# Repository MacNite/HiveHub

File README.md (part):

# HiveHub

> **Project renamed: HiveScale → HiveHub.** The project outgrew its original
> "dual scale" scope and now acts as a **data collector / hub for many different
> types of beehive sensors and scales** (up to 18 hives per ESP32), so the name
> was changed to match. A few internal identifiers — the database measurement
> columns, the OTA `target` value, the Docker image name (`…/hivescale-api`), the
> device's stored-config (NVS) namespace and MQTT topics — still use the old
> `hivescale` name on purpose: changing them would need data/firmware migrations
> and could strand existing measurements or deployed-device config. The
> third-party **beehivemonitoring.com "HiveScale"** wireless weight scale is an
> unrelated product and keeps its own name.

**Hardware status: all published PCBs are tested and working.** The recommended build is the **XIAO ESP32-C6 on the Scale Module V0.4** with **NAU7802**, **MAX17048**, **TPS63020**, **TP4056**, RTC, SD card and SHT40 — optionally expanded to **16 scales** with the NAU7802 breakout PCB (TCA9548A mux + up to 8× NAU7802). See [pcb-design/README.md](pcb-design/README.md). The old ESP32 30-pin board is obsolete and no longer recommended.

**HiveHub is an ESP32-based data collector for beehive sensors and scales.** It
gathers weight, temperature, humidity, sound, vibration, power state, and network
state from one or more hives (up to 18 per ESP32) and sends the readings to a
self-hosted FastAPI backend backed by PostgreSQL, where they can be displayed in
[HivePal](https://github.com/martinhrvn/hive-pal).

### Natively supported sensors

Every sensor is optional and compiled in per device — HiveHub reads the
following directly on the ESP32:

- **Ambient sensor (SHT4x / SHT3x / BME280)** — one device-level outside-hive
  sensor on the shared I2C bus, selectable at build time: SHT4x/SHT40 (default)
  or SHT3x for temperature + humidity, or a BME280 which additionally reports
  barometric pressure (`ambient_pressure_hpa`).
- **DS18B20** — per-hive in-hive temperature probes (1-Wire).
- **INMP441** — in-hive sound via I2S MEMS microphones with per-band FFT.
- **MAX17048** — LiPo battery voltage, state-of-charge, and low-battery alerts (I2C).
- **Wired load cells via HX711 or NAU7802** — the hive scales themselves; NAU7802
  over I2C (optionally behind a TCA9548A mux) scales to many channels for
  multi-hive setups.

On top of these wired sensors, HiveHub also bridges a range of wireless BLE/GATT
sensors and scales (HolyIot, RuuviTag, HiveInside, and beehivemonitoring.com
HiveHeart / HiveScale devices) — see [Features](#features) below.

> 🌐 **Website & setup guide:** a small static site lives in [`website/`](website/) — a
> feature overview, a step-by-step setup guide, a complete
> ["Build your own" guide](website/build.html) (BOM with price estimates, wiring,
> firmware, backend — downloadable as PDF), and an in-browser
> [`secrets.h` configurator](website/configurator.html) that builds your firmware
> config (sensors, BLE/GATT options, power modules) without hand-editing macros.
> It deploys to GitHub Pages via `.github/workflows/pages.yml`
> (enable **Settings → Pages → Source: GitHub Actions**), e.g.
> `https://macnite.github.io/HiveHub/`.

---

## Features

Every sensor is optional and compiled in per device — start with weight and add the rest.

- **Dual load cells** — two HX711 amplifiers drive two independent hive scales (the one always-on measurement).
- **Backend load-cell temperature compensation** — corrects HX711 thermal drift on read from the stored raw values; see [docs/temperature-compensation.md](docs/temperature-compensation.md).
- **Per-hive temperature** — optional DS18B20 probes on a shared 1-Wire bus (off by default), or an in-hive BLE sensor as the source.
- **Per-hive in-hive sound** — optional INMP441 stereo I2S microphones with per-band FFT (off by default).
- **Per-hive vibration** — from a paired in-hive BLE sensor (a HiveInside nRF54LM20A gives full FFT bands; a HolyIot/RuuviTag beacon gives a low-rate magnitude), capturing the ~20 Hz pre-swarm signal microphones miss. (The old wired LIS3DH/LIS2DH12 driver has been removed — in-hive vibration is BLE-only.)
- **In-hive BLE sensors** — pair up to two battery beacons (HolyIot 25015, RuuviTag, HiveInside nRF54LM20A, or beehivemonitoring.com HiveHeart) for temperature/humidity/pressure/vibration with no wiring. Note that a HiveHeart is read over GATT and accepts only **one** connection at a time, so HiveHub, the beehivemonitoring Hub and the beehivemonitoring app cannot share one — see [beehivemonitoring-gatt.md](docs/beehivemonitoring-gatt.md#one-reader-at-a-time).
- **Ambient temperature & humidity** — one selectable device-level I2C sensor: SHT4x/SHT40 (default), SHT3x, or a BME280 that also reports barometric pressure (`ambient_pressure_hpa`). Picked at build time (`ENABLE_SHT4X_AMBIENT` / `ENABLE_SHT3X_AMBIENT` / `ENABLE_BME280_AMBIENT`).
- **RTC timekeeping** — a DS3231 timestamps measurements without depending on NTP.
- **SD card cache & backup** — local buffering when uploads fail, plus an append-only persistent backup that can be downloaded in AP mode and re-imported via HivePal.
- **Claim-code pairing** — claim devices from HivePal without manual database setup.
- **Remote configuration & commands** — sampling interval, scale offsets/factors, calibration, OTA checks, provisioning, reboot, Wi-Fi reset, and factory reset.
- **OTA firmware updates** — owner-scoped releases with an accept-to-apply gate; the device also relays firmware over BLE GATT to a HiveInside sensor or a HiveTraffic counter. Both relays are version-gated and explicit: publishing a release never pushes it to a sub-device on its own.
- **Wi-Fi provisioning portal** — opened by the setup button (or remotely with a `start_provisioning` command) for field configuration, including pairing wireless sensors.
- **[Inspection mode](docs/inspection-mode.md)** — one press of the external button, a dashboard switch or a HivePal API call marks the window while a hive is open, so the 40 kg step from lifting two supers stays out of the charts, insights and alert rules. Nothing is deleted: the readings remain in the database and in every export.
- **Multi-network Wi-Fi** — up to three saved networks.
- **Hive audio (optional)** — ask a paired HiveInside node (firmware 0.6.2+) to record 10–60 seconds from inside the hive, then play it back in the dashboard. The hub collects the request on its next wake, so a recording arrives within one reporting interval rather than instantly. Authenticated with a shared key and stored as WAV on your own server. Useful for checking what an insight flagged — or just for listening to the bees. See [Listening to a hive](docs/audio-recording.md).
- **Insights** — backend auto-evaluation of weight, temperature, sound, vibration, and entrance traffic per hive, based on [these publications](docs/insights-sources-tldr.md).
- **Insight alert notifications (optional)** — get swarm / robbing / winter-risk alerts by **e-mail (SMTP)** and/or **Web Push** to your phone or an installable dashboard PWA (Android, iOS 16.4+, desktop) when an insight first fires or escalates. Off by default; see [Insight alert notifications](docs/notifications.md).
- **Optional off-grid mode** — solar/LiPo charging (CN3791 MPPT + TPS63020) with MAX17048 LiPo telemetry.
- **Optional entrance bee counters** — wireless [HiveTraffic](docs/hivetraffic-bee-counter.md) counters over **BLE/GATT only** (wired I2C BeeCounters are no longer supported).
- **Built-in web dashboard (optional)** — a dependency-free dashboard served from the backend at `/dashboard` for single-owner self-hosts, protected by **username + password login** (first visit runs a setup wizard; admin/viewer roles): cross-device hive comparison, charts for every data group, plus device-config editing, hive renaming, firmware/OTA and calibration controls, SD-backup import, and user management. Off by default (`ENABLE_LOCAL_DASHBOARD`); see [server/dashboard/README.md](server/dashboard/README.md) and the [live demo](https://macnite.github.io/HiveHub/dashboard-demo/).
- **Publish data for your website** — from **Device & admin → Publish data**, publish one chart (a metric, the hives you pick, a rolling period) and embed it in a club page, blog or shop with a one-line `<iframe>` — or fetch the same slice as JSON/CSV and draw it yourself. Everything else stays behind the login: a published link exposes only the labels you typed, no device IDs or other readings, and can be revoked at any time. See [Publish data](docs/publish-embed.md).
- **[HivePal](https://github.com/martinhrvn/hive-pal) integration** — dedicated `/api/v1/app/...` endpoints using a HivePal service key, per-user JWTs, and per-user access roles.
- **Optional MQTT bridge** — mirror every reading to an MQTT broker (Home Assistant, Node-RED, openHAB…) with Home Assistant auto-discovery, alongside the built-in PostgreSQL store. Off by default; see [MQTT / Home Assistant integration](#mqtt--home-assistant-integration).
- **PCB designs (tested and working)** — KiCad ESP32-C6 Scale Module (recommended) and NAU7802 breakout board with fabrication outputs, plus the Power Module and legacy 30-pin Scale Module.
- **Docker Compose deployment** — the API and PostgreSQL database.

---

## Repository structure

```text
HiveHub/
├── firmware/                   # ESP32 PlatformIO project (src/, include/)
├── server/                     # Python FastAPI backend, insights, migrations
│   ├── dashboard/              # Built-in login-protected web dashboard (served at /dashboard)
│   └── embed/                  # Public "Publish data" chart pages (served at /embed/chart/<token>)
├── docker/                     # Docker Compose deployment
├── website/                    # Static site + secrets.h configurator (GitHub Pages)
│   └── dashboard-demo/         # Backend-free dashboard demo (sample data)
├── docs/                       # Hardware, API, deployment, and feature docs
├── pcb-design/                 # KiCad breakout PCB design and fabrication files
├── test-data/                  # Mock server and decoder/insight unit tests
└── .github/workflows/          # CI: backend image build + website Pages deploy
```

---

## Hardware

### Core components

All links are affiliate links and support this project directly.

The recommended build is the **XIAO ESP32-C6 on the Scale Module V0.4** — the complete
bill of materials with price estimates and shop links lives on the
[**Build your own** page](website/build.html) (also downloadable as
[CSV](website/assets/hivehub-bom.csv)).

| Component | Role |
|---|---|
| Seeed Studio XIAO ESP32-C6 | Main controller (**recommended** — plugs into the Scale Module V0.4 PCB) |
| NAU7802 (I2C, on the Scale Module / breakout PCB) + [load cells](https://s.click.aliexpress.com/e/_c33VsCl7) | Weight measurement (**recommended** — 2 scales on the Scale Module, up to 16 via the NAU7802 breakout PCB with its TCA9548A mux + up to 8× NAU7802) |
| [SHT4x / SHT40](https://s.click.aliexpress.com/e/_c3CvaIKz) (or SHT3x / BME280) | Ambient temperature and humidity (BME280 also adds barometric pressure) |
| [DS3231 RTC](https://s.click.aliexpress.com/e/_c4mfPBtR) | Offline timekeeping (remove its 4.7 kΩ I2C pull-ups — see the I2C pull-up note in [docs/wiring.md](docs/wiring.md)) |
| [MicroSD card module](https://s.click.aliexpress.com/e/_c3oDcFM9) + card | Local cache and backup storage |
| [MAX17048](https://s.click.aliexpress.com/e/_c3JKEzrL) | LiPo battery gauge (on the Scale Module) |
| [TPS63020 buck-boost](https://s.click.aliexpress.com/e/_c2uscIy1) | Battery/5 V input to the regulated 3.3 V rail |
| [TP4056 USB-C charger](https://s.click.aliexpress.com/e/_c4beU1nL) | LiPo charging |
| [Momentary pushbutton](https://s.click.aliexpress.com/e/_c4sqg7Lx) | Provisioning and factory reset |
| [IP-rated enclosure](https://s.click.aliexpress.com/e/_c30msn9R), [glands](https://de.aliexpress.com/item/1005007921366362.html), frame hardware | Outdoor installation |
| [ESP32 Dev Board](https://s.click.aliexpress.com/e/_c3LV3nfF) + 2x [HX711](https://s.click.aliexpress.com/e/_c3DkGsAN) | Legacy 30-pin build (obsolete — no longer recommended) |

### Optional sensors (enable per device in `secrets.h`)

| Component | Firmware flag | Role |
|---|---|---|
| 2x [DS18B20 waterproof probes](https://s.click.aliexpress.com/e/_c4X4ktmv) | `ENABLE_DS18B20_HIVE_TEMP` | Internal hive temperature (or use an in-hive BLE sensor) |
| 2x [INMP441 sound sensors](https://s.click.aliexpress.com/e/_c313NoAd) | `ENABLE_INMP441_MICS` | Internal hive sound with per-band FFT |
| [MAX17048](https://s.click.aliexpress.com/e/_c3JKEzrL) | `ENABLE_MAX17048_BATTERY` | LiPo voltage, state-of-charge, and low-battery alert |
| In-hive BLE sensor (HolyIot 25015 / RuuviTag / HiveInside / HiveHeart) | `ENABLE_BLE_SCAN`, `ENABLE_BEEHIVE_GATT` | Temp / humidity / pressure / vibration, no wiring — paired by MAC |
| [CN3791 solar charger](https://s.click.aliexpress.com/e/_c4T7Ve5x) · [10 Ah LiPo](https://s.click.aliexpress.com/e/_c45jfAGv) · [6 V 4.5 W solar panel](https://s.click.aliexpress.com/e/_c3njKuVF) | Hardware only | Off-grid charging path feeding the Scale Module's TPS63020 |

### Optional bee counters

Entrance traffic counting (in/out bees) is **BLE/GATT-only**:

- **HiveTraffic** — the wireless [2026-easy-bee-counter](https://github.com/MacNite/2026-easy-bee-counter) board; see [docs/hivetraffic-bee-counter.md](docs/hivetraffic-bee-counter.md). Pairable to any hive.
- Wired I2C BeeCounters (the old `0x30`/`0x31` slave path, including firmware updates over I2C) are **no longer supported**. BeeCounter firmware is updated over BLE GATT instead — see [hivetraffic-bee-counter.md](docs/hivetraffic-bee-counter.md).

### Firmware pin mapping

Pins are defined in `firmware/include/config.h` (with optional per-device overrides in `secrets.h`). The firmware source is split into focused units under `firmware/src/` (`main.cpp`, `hivehub_network.cpp`, `portal.cpp`, `sensors.cpp`, `scale_bus.cpp`, `i2c_bus.cpp`, `hive_config.cpp`, `mics.cpp`, `ble_sensor.cpp`, `beehive_gatt.cpp`, `bee_counter_client.cpp`, `storage_power.cpp`, `device_prefs.cpp`, `status_led.cpp`, `globals.cpp`).

The table below is the **legacy 30-pin ESP32** map. The recommended **XIAO ESP32-C6** build (`pio run -e xiao_esp32c6`) has its own pin map — NAU7802 scales over I2C on D4/D5, DS18B20 on D1, SD on D3/D8–D10, button on D2, no HX711/INMP441 — see [docs/wiring.md](docs/wiring.md) and [pcb-design/README.md](pcb-design/README.md).

| Signal | GPIO | Notes |
|---|---:|---|
| HX711 #1 DOUT / SCK | 16 / 17 | Scale 1; SCK held high during deep sleep to power down the HX711 |
| HX711 #2 DOUT / SCK | 32 / 33 | Scale 2; SCK held high during deep sleep to power down the HX711 |
| DS18B20 1-Wire data | 4 | Shared bus for both probes; 4.7 kΩ pull-up to 3.3 V (`ENABLE_DS18B20_HIVE_TEMP`) |
| I2C SDA / SCL | 21 / 22 | RTC, SHT4x, NAU7802/TCA9548A, optional MAX17048 — shared bus at an explicit **100 kHz** |
| SD CS / SCK / MISO / MOSI | 5 / 18 / 23 / 19 | MicroSD over SPI |
| Setup button | 27 | `INPUT_PULLUP`; short press opens provisioning AP, long press factory resets |

> On the **XIAO ESP32-C6** (firmware 0.25.0+) the setup button is the board's on-board USER/BOOT button, and the external D2 button is the [inspection button](docs/inspection-mode.md). The 30-pin board above is unchanged. Note that GPIO9 cannot wake the C6 from deep sleep and holding it at power-up enters the serial bootloader, so on that board press and hold the USER button and the AP opens a second into the next wake (up to one send interval away) — or press RESET, release it, *then* hold BOOT to get there in under a minute (never hold BOOT across the RESET: that is the flashing gesture). For a sealed hub use **Start AP mode** in the dashboard — see [docs/ap-mode-sd-download.md](docs/ap-mode-sd-download.md).
| INMP441 BCLK / WS / SD | 14 / 13 / 34 | I2S, shared by both mics; GPIO34 is input-only (`ENABLE_INMP441_MICS`) |

> See [docs/wiring.md](docs/wiring.md) for detailed wiring and [pcb-design/README.md](pcb-design/README.md) for the KiCad breakout PCB pinout.

---

## Firmware setup

### Prerequisites

- PlatformIO (VS Code extension or CLI).

### Configuration

```bash
cp firmware/include/secrets.example.h firmware/include/secrets.h
```

Edit `firmware/include/secrets.h`:

```cpp
#define DEVICE_ID           "hive-001"
#define API_KEY             "your-api-key-here"   // unique per device — see note below
#define CLAIM_CODE          "ABCD-1234"
#define CLAIM_CODE_REVISION 1
#define API_BASE_URL        "https://your-backend-domain.com"   // HTTPS (TLS is verified)

#define WIFI1_SSID          "your-wifi-ssid-1"
#define WIFI1_PASS          "your-wifi-password-1"
// WIFI2_* and WIFI3_* are optional fallbacks
```

Values in `secrets.h` seed the device's persistent `Preferences` on first boot. Later changes are usually made through the backend or provisioning portal. Set `FORCE_RESEED true` only when you intentionally want to overwrite stored preferences from the build file.

> **Per-device API key:** give each device its own unique `API_KEY` (generate one
> with `openssl rand -hex 32`). The backend registers the key against the device's
> `device_id` on first contact and rejects mismatches afterwards, so a leaked key
> only affects that one device. It no longer has to match the server's `API_KEY`
> environment variable — that value is now only the master/admin key for tooling.

### TLS / certificate verification

The firmware verifies the backend's TLS certificate. It ships the ISRG Root X1
(Let's Encrypt) root CA in `firmware/include/ca_cert.h` and syncs the clock over
NTP after connecting so validity can be checked. Therefore:

- By default, the backend must be reachable over **HTTPS with a valid certificate** (a reverse proxy with Let's Encrypt is the simplest setup).
- For a CA other than Let's Encrypt, replace the certificate in `firmware/include/ca_cert.h` (instructions are in that file).
- NTP (UDP port 123) must be reachable from the device's network.

For a trusted LAN deployment that cannot use TLS, add the following **firmware
build setting** to `secrets.h` and use an `http://` `API_BASE_URL` (for example,
`http://192.168.1.10:31115`). This is intentionally not a server environment
variable: the ESP32 selects its transport before it can contact the server.

```cpp
#define ALLOW_INSECURE_HTTP 1
```

The opt-in keeps HTTPS working and certificate-verified, but also permits HTTP
for API requests and OTA downloads. HTTP exposes the per-device API key,
measurements, commands, and firmware image to anyone able to observe or alter
traffic, so use it only on an isolated, trusted network.

### Optional modules

Optional sensors are enabled per build in `secrets.h`. The defaults shipped in `secrets.example.h`:

```cpp
#define ENABLE_DS18B20_HIVE_TEMP 0   // wired in-hive temperature probes (default off)
#define ENABLE_INMP441_MICS      0   // stereo I2S mics + per-band FFT (default off)
#define ENABLE_BLE_SCAN          1   // in-hive BLE sensor bridge — HolyIot/RuuviTag/HiveInside (default on)
#define ENABLE_BEEHIVE_GATT      0   // beehivemonitoring.com HiveHeart / HiveScale over GATT (default off)
#define ENABLE_MAX17048_BATTERY  0   // LiPo fuel-gauge telemetry (default off)
```

The [secrets.h configurator](website/configurator.html) writes these (and the wireless-sensor macros) for you.

> Cellular (SIM7080G) transport is no longer part of this firmware. LTE, solar,
> and battery handling now live on a separate **Power Module** that connects to
> the Scale Module over I2C/ESP-NOW. The ESP32 firmware itself is Wi-Fi only.

### Download a prebuilt image (no toolchain)

Every CI run builds both targets and attaches the images to the run, and every
tagged release carries them permanently:

| Where | What you get | Keeps |
|---|---|---|
| [Releases](../../releases) | Images for the tagged version | forever |
| [Actions → CI](../../actions/workflows/ci.yml) → a run → *Artifacts* | Images for that exact commit, incl. branches and PRs | 90 days |

Two files per board — `esp32-c6` (XIAO, recommended) and `esp32` (legacy 30-pin):

- **`hivehub_<board>_<version>_full.bin`** — bootloader + partition table +
  otadata + application, written as a single file at offset `0x0`. Use this for
  a blank board.
- **`hivehub_<board>_<version>.bin`** — application image only. This is the file
  to upload to your backend for OTA, or to the dashboard's firmware uploader.

```bash
# XIAO ESP32-C6, blank board
esptool.py --chip esp32c6 --port /dev/ttyACM0 write_flash 0x0 hivehub_esp32-c6_0.24.7_full.bin

# Legacy 30-pin ESP32
esptool.py --chip esp32 --port /dev/ttyUSB0 write_flash 0x0 hivehub_esp32_0.24.7_full.bin
```

Prebuilt images contain no `secrets.h`: Wi-Fi, server URL and API key are set on
the device through the [setup portal](#wi-fi-provisioning-portal), and the
compile-time feature flags stay at their defaults. To change a flag (DS18B20,
INMP441 mics, GATT sensors …) you still need a local build.

`firmware/ci/package_build.sh <env>` produces the same files locally after a
`pio run`.

### Flash from source

```bash
cd firmware
pio run --target upload
pio device monitor   # 115200 baud
```

### PlatformIO dependencies

`platformio.ini` installs the required libraries automatically:

- `bogde/HX711`, `paulstoffregen/OneWire`, `milesburton/DallasTemperature`
- `adafruit/Adafruit SHT4x Library`, `adafruit/RTClib`, `bblanchon/ArduinoJson`
- `kosme/arduinoFFT` — per-band FFT for the INMP441 mics and the vibration bands
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
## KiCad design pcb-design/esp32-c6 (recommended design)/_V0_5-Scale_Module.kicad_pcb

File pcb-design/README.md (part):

# HiveHub PCB design

**Current state (as of 9 July 2026): all published PCBs are tested and working.**

## Recommended setup

- Use the **XIAO ESP32-C6 on the Scale Module (V0.4)** as your main HiveHub controller, populated with the recommended module set: **NAU7802** (2 scales), **MAX17048** battery gauge, **TPS63020** buck-boost, **TP4056** USB-C charger, **DS3231 RTC**, **micro-SD module** and **SHT40**. It also collects data from up to 16 BLE in-hive sensors.
- **Optional, for 3+ scales:** add the **NAU7802 breakout PCB (v0.2)** *without* an MCU — its **TCA9548A** I2C multiplexer carries up to **8× NAU7802** for up to **16 wired scales** in total. When the breakout/mux is used, install **no NAU7802 on the Scale Module** (all NAU7802s share I2C address `0x2A` and would collide).
- You can also populate the NAU7802 breakout PCB *with* a XIAO MCU and run it as a **standalone BLE scale sensor** with up to 16 scales. Do **not** use the breakout with an MCU as a HiveHub itself — it has no RTC and no SD card.
- The **ESP32 30-pin Scale Module** is **no longer recommended** — it is obsolete and will be discontinued soon.
- The **Power Module** still works, but it will **probably be discontinued soon** in favour of powering the C6 Scale Module directly.

> **Power jumper:** the Scale Module's 1×3 power-selection header chooses the
> supply path — jumper in the **top position when powered from a battery**
> (via the TPS63020), **bottom position when powered from a 5 V power supply**.

## Boards in this directory

| Directory | Board | Version | Status |
|---|---|---|---|
| `scale module/esp32-c6/` | Scale Module — XIAO ESP32-C6 | **V0.4** | ✅ **Recommended** — tested and working |
| `NAU7802 breakout pcb/` | NAU7802 breakout (16-scale I2C frontend) | **v0.2** | ✅ Recommended — tested and working |
| `power module/` | Power Module (solar / battery / connectivity) | **V0.3** | ⚠️ Tested and working — probably discontinued soon |
| `scale module/esp32 (30 pin)/` | Scale Module — ESP32 30-pin DevKit | **V0.3** | ❌ Obsolete — no longer recommended, will be discontinued |

Each board folder contains the KiCad project (`.kicad_pro` / `.kicad_sch` / `.kicad_pcb`) and ready-to-order Gerber/drill outputs in its `fabrication/` subdirectory.

---

## Scale Module — XIAO ESP32-C6 (V0.4) — recommended

The central board of a HiveHub. A breakout board that accepts off-the-shelf modules on pin headers — no SMD soldering required. Built around the compact **Seeed Studio XIAO ESP32-C6** (RISC-V, Wi-Fi 6 + BLE), it uses only the 11 front-header pins (D0–D10).

Scales are read over I2C via the **on-board NAU7802** 24-bit load-cell ADC (2 differential channels = 2 scales). More wired scales are added with the NAU7802 breakout PCB on the I2C expansion header (up to 16 muxed channels). There is **no HX711 and no INMP441 microphone** on this board — use paired BLE in-hive sensors for acoustics and vibration.

### On board

| Module / connector | Interface | Notes |
|---|---|---|
| XIAO ESP32-C6 | — | Main controller, plugs into socket headers |
| NAU7802 | I2C `0x2A` | Load-cell ADC — 2 scale channels with screw-terminal load-cell inputs |
| DS3231 RTC | I2C `0x68` | Timekeeping with coin-cell backup |
| SHT40 Ambient | I2C `0x44` | Ambient temperature and humidity |
| SD module | SPI | MicroSD for local cache and backup |
| DS18B20 header | 1-Wire (D1) | In-hive temperature bus, 4.7 kΩ pull-up on board |
| BeeCounter header | — | Unused: wired I2C BeeCounters are no longer supported by the firmware. Entrance counting is now BLE/GATT-only (HiveTraffic); the header is a leftover on this board revision. |
| MAX17048 | I2C | LiPo battery voltage / state-of-charge gauge |
| TPS63020 buck-boost | — | Battery/solar input to regulated 3.3 V rail, with power selector |
| Power Module header | — | Connection to the separate Power Module (optional) |
| I2C expansion header | I2C | For the NAU7802 breakout PCB and other I2C devices |
| Setup pushbutton | Digital (D2) | Short press: provisioning AP · long press: factory reset |

### Firmware pin map (from `firmware/include/config.h`, `[env:xiao_esp32c6]`)

| Signal | XIAO pin | GPIO | Notes |
|---|---|---:|---|
| DS18B20 1-Wire | D1 | 1 | In-hive temperature bus (4.7 kΩ pull-up on board) |
| I2C SDA | D4 | 22 | NAU7802 scales, RTC, SHT40, MAX17048, expansion (100 kHz) |
| I2C SCL | D5 | 23 | Shared I2C bus clock |
| SD CS | D3 | 21 | SD card chip select |
| SD SCK / MISO / MOSI | D8 / D9 / D10 | 19 / 20 / 18 | MicroSD over SPI |
| Setup button | D2 | 2 | Button to GND, `INPUT_PULLUP`; deep-sleep GPIO wake |
| (unused) | D0 | 0 | Free |

> **Antenna:** the XIAO ESP32-C6 has a built-in ceramic antenna and a u.FL connector. The firmware drives the on-board RF switch (GPIO3 enable, GPIO14 select) and defaults to the built-in antenna; set `XIAO_C6_USE_EXTERNAL_ANTENNA 1` in `secrets.h` for the u.FL antenna.

Build the firmware with `pio run -e xiao_esp32c6`.

---

## NAU7802 breakout PCB (v0.2)

I2C load-cell frontend: **8× NAU7802** behind **TCA9548A** I2C multiplexers, for up to **16 scales** (each NAU7802 reads 2 load cells). Connects to the Scale Module's I2C expansion header.

Two ways to populate it:

- **Without an MCU (recommended):** a pure I2C scale expander for a HiveHub. The NAU7802 has a fixed address (`0x2A`), so the mux is what makes more than one chip per bus possible — see [docs/multi-hive.md](../docs/multi-hive.md) for the bus topology and firmware behaviour.
- **With a XIAO MCU (optional footprint):** a standalone battery-powered **BLE scale sensor** broadcasting up to 16 scale readings to a HiveHub. Do not use this as a full HiveHub — the board has no RTC and no SD card, so it cannot timestamp or cache measurements offline.

Solder jumpers select the bus/power options; see the schematic before assembly.

---

## Power Module (V0.3) — probably discontinued soon

Handles off-grid power for a Scale Module: solar charging, battery, regulated output, and a header to the Scale Module (I2C/ESP-NOW). Tested and working, but with the ESP32-C6 Scale Module carrying its own TPS63020 regulator and MAX17048 fuel gauge, this separate board will **probably be discontinued soon**. Prefer powering the C6 Scale Module directly.

---

## Scale Module — ESP32 30-pin (V0.3) — obsolete

> ❌ **No longer recommended.** This board and its firmware target (`pio run -e esp32dev`) keep working, but the design is obsolete and will be discontinued soon. Use the ESP32-C6 Scale Module for new builds. The reference below is retained for existing boards.

Breakout board for a 30-pin ESP32 DevKit with the full wired sensor suite: 2× HX711 scale amplifiers, DS18B20 1-Wire bus, 2× INMP441 I2S microphones, SD, RTC, and SHT40. (The board also carries a legacy BeeCounter header, but wired I2C BeeCounters are no longer supported by the firmware — entrance counting is BLE/GATT-only now.)

### Modules on board

| Ref | Module | Interface | Notes |
|---|---|---|---|
| J1, J2 | ESP32 30-pin Dev Board | — | Main controller; plugs into left and right header rows |
| J4, J7 | HX711 Scale 1 | Digital I/O | Load cell amplifier for scale platform 1 |
| J3, J8 | HX711 Scale 2 | Digital I/O | Load cell amplifier for scale platform 2 |
| J11 | Load cell 1 input | Screw terminal | Direct load cell wires for scale 1 |
| J12 | Load cell 2 input | Screw terminal | Direct load cell wires for scale 2 |
| J9 | SD module | SPI | MicroSD card for local cache and backup |
| J5 | DS3231 RTC | I2C | Real-time clock with coin cell backup |
| J13 | DS18B20 Hive 1 | 1-Wire | Internal hive temperature probe |
| J14 | DS18B20 Hive 2 | 1-Wire | Internal hive temperature probe |
| J15 | SHT40 Ambient | I2C | External ambient temperature and humidity |
| J6 | INMP441 Sound Sensor Hive 1 | I2S | MEMS microphone — left channel |
| J16 | INMP441 Sound Sensor Hive 2 | I2S | MEMS microphone — right channel |
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
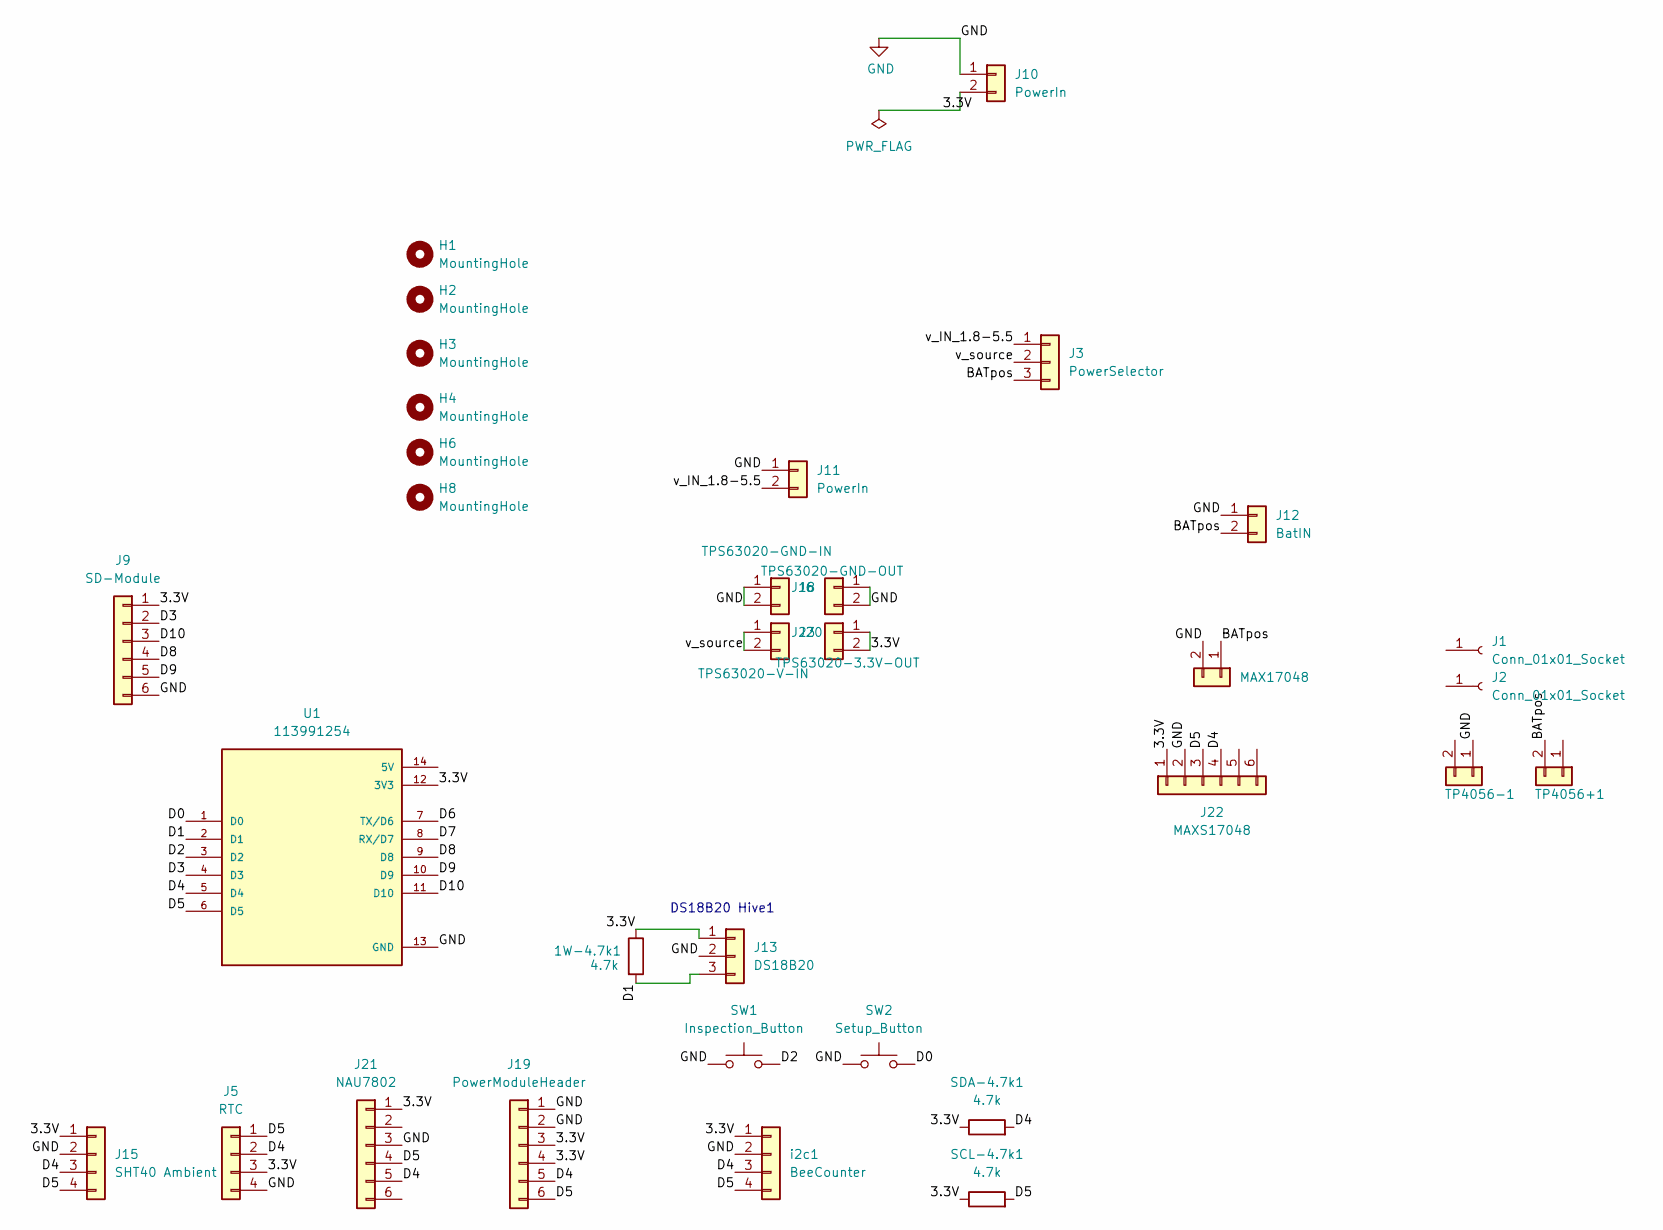
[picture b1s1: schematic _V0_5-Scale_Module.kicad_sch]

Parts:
1W-4.7k1: 4.7k; R_Axial_DIN0207_L6.3mm_D2.5mm_P7.62mm_Horizontal
H1, H2, H3, H4, H6, H8: MountingHole; MountingHole_3.2mm_M3
J1, J2: Conn_01x01_Socket; PinSocket_1x01_P2.54mm_Vertical
J3: PowerSelector; PinHeader_1x03_P2.54mm_Vertical
J5: RTC; PinSocket_1x04_P2.54mm_Vertical
J6: TPS63020-GND-IN; PinSocket_1x02_P2.54mm_Vertical
J9: SD-Module; PinSocket_1x06_P2.54mm_Vertical
J10, J11: PowerIn; TerminalBlock_Xinya_XY308-2.54-2P_1x02_P2.54mm_Horizontal
J12: BatIN; TerminalBlock_Xinya_XY308-2.54-2P_1x02_P2.54mm_Horizontal
J13: DS18B20; JST_XH_B3B-XH-A_1x03_P2.50mm_Vertical
J15: SHT40 Ambient; JST_XH_B4B-XH-A_1x04_P2.50mm_Vertical
J18: TPS63020-GND-OUT; PinSocket_1x02_P2.54mm_Vertical
J19: PowerModuleHeader; PinSocket_1x06_P2.54mm_Vertical
J20: TPS63020-V-IN; PinSocket_1x02_P2.54mm_Vertical
J21: NAU7802; PinSocket_1x06_P2.54mm_Vertical
J22: MAXS17048; PinSocket_1x06_P2.54mm_Vertical
J23: TPS63020-3.3V-OUT; PinSocket_1x02_P2.54mm_Vertical
MAX17048: BatteryMAX17048; PinSocket_1x02_P2.54mm_Vertical
SCL-4.7k1: 4.7k; R_Axial_DIN0207_L6.3mm_D2.5mm_P7.62mm_Horizontal
SDA-4.7k1: 4.7k; R_Axial_DIN0207_L6.3mm_D2.5mm_P7.62mm_Horizontal
SW1: Inspection_Button; PinSocket_1x02_P2.54mm_Vertical
SW2: Setup_Button; PinSocket_1x02_P2.54mm_Vertical
TP4056+1, TP4056-1: BatteryMAX17048; PinSocket_1x02_P2.54mm_Vertical
U1: 113991254; MODULE_113991254; PARTREV v1.0
i2c1: BeeCounter; JST_XH_B4B-XH-A_1x04_P2.50mm_Vertical

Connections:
/3.3V: 1W-4.7k1.1, J5.3, J9.1, J10.2, J13.1, J15.1, J19.3, J19.4, J21.1, J22.1, J23.1, J23.2, SCL-4.7k1.1, SDA-4.7k1.1, U1.12 (3V3), i2c1.1
/BATpos: J3.3, J12.2, MAX17048.1, TP4056+1.2 (Pin_2_2)
/D0: SW2.2, U1.1 (D0); also elsewhere on the board
/D1: 1W-4.7k1.2, J13.3, U1.2 (D1)
/D2: SW1.2, U1.3 (D2); also elsewhere on the board
/D3: J9.2, U1.4 (D3)
/D4: J5.2, J15.3, J19.5, J21.5, J22.4, SDA-4.7k1.2, U1.5 (D4), i2c1.3
/D5: J5.1, J15.4, J19.6, J21.4, J22.3, SCL-4.7k1.2, U1.6 (D5), i2c1.4
/D6: U1.7 (TX/D6)
/D7: U1.8 (RX/D7)
/D8: J9.4, U1.9 (D8)
/D9: J9.5, U1.10 (D9)
/D10: J9.3, U1.11 (D10)
/v_IN_1.8-5.5: J3.1, J11.2
/v_source: J3.2, J20.1, J20.2
GND: J5.4, J6.1, J6.2, J9.6, J10.1, J11.1, J12.1, J13.2, J15.2, J18.1, J18.2, J19.1, J19.2, J21.3, J22.2, MAX17048.2, SW1.1, SW2.1, TP4056-1.1 (Pin_1_1), U1.13 (GND), i2c1.2; also elsewhere on the board

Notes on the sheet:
DS18B20 Hive1

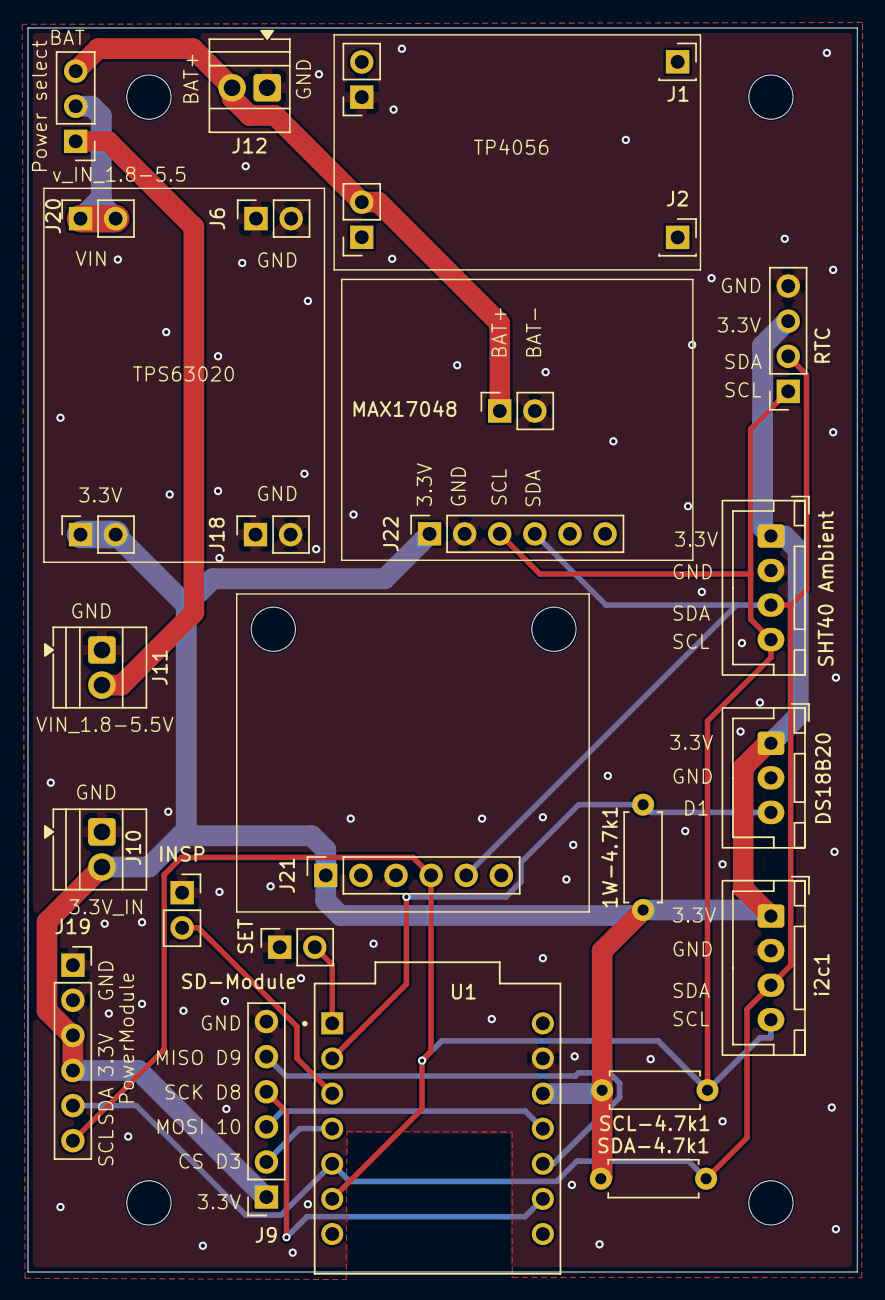
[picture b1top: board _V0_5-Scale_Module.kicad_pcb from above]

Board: 2 copper layers, 60.0 x 90.0 mm, 33 parts (0 on the bottom side), 14 nets.

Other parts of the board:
INSP: Inspection_Button; PinSocket_1x02_P2.54mm_Vertical
SET: Setup_Button; PinSocket_1x02_P2.54mm_Vertical

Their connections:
/D0: SET.2; also elsewhere on the board
/D2: INSP.2; also elsewhere on the board
GND: INSP.1, SET.1; also elsewhere on the board

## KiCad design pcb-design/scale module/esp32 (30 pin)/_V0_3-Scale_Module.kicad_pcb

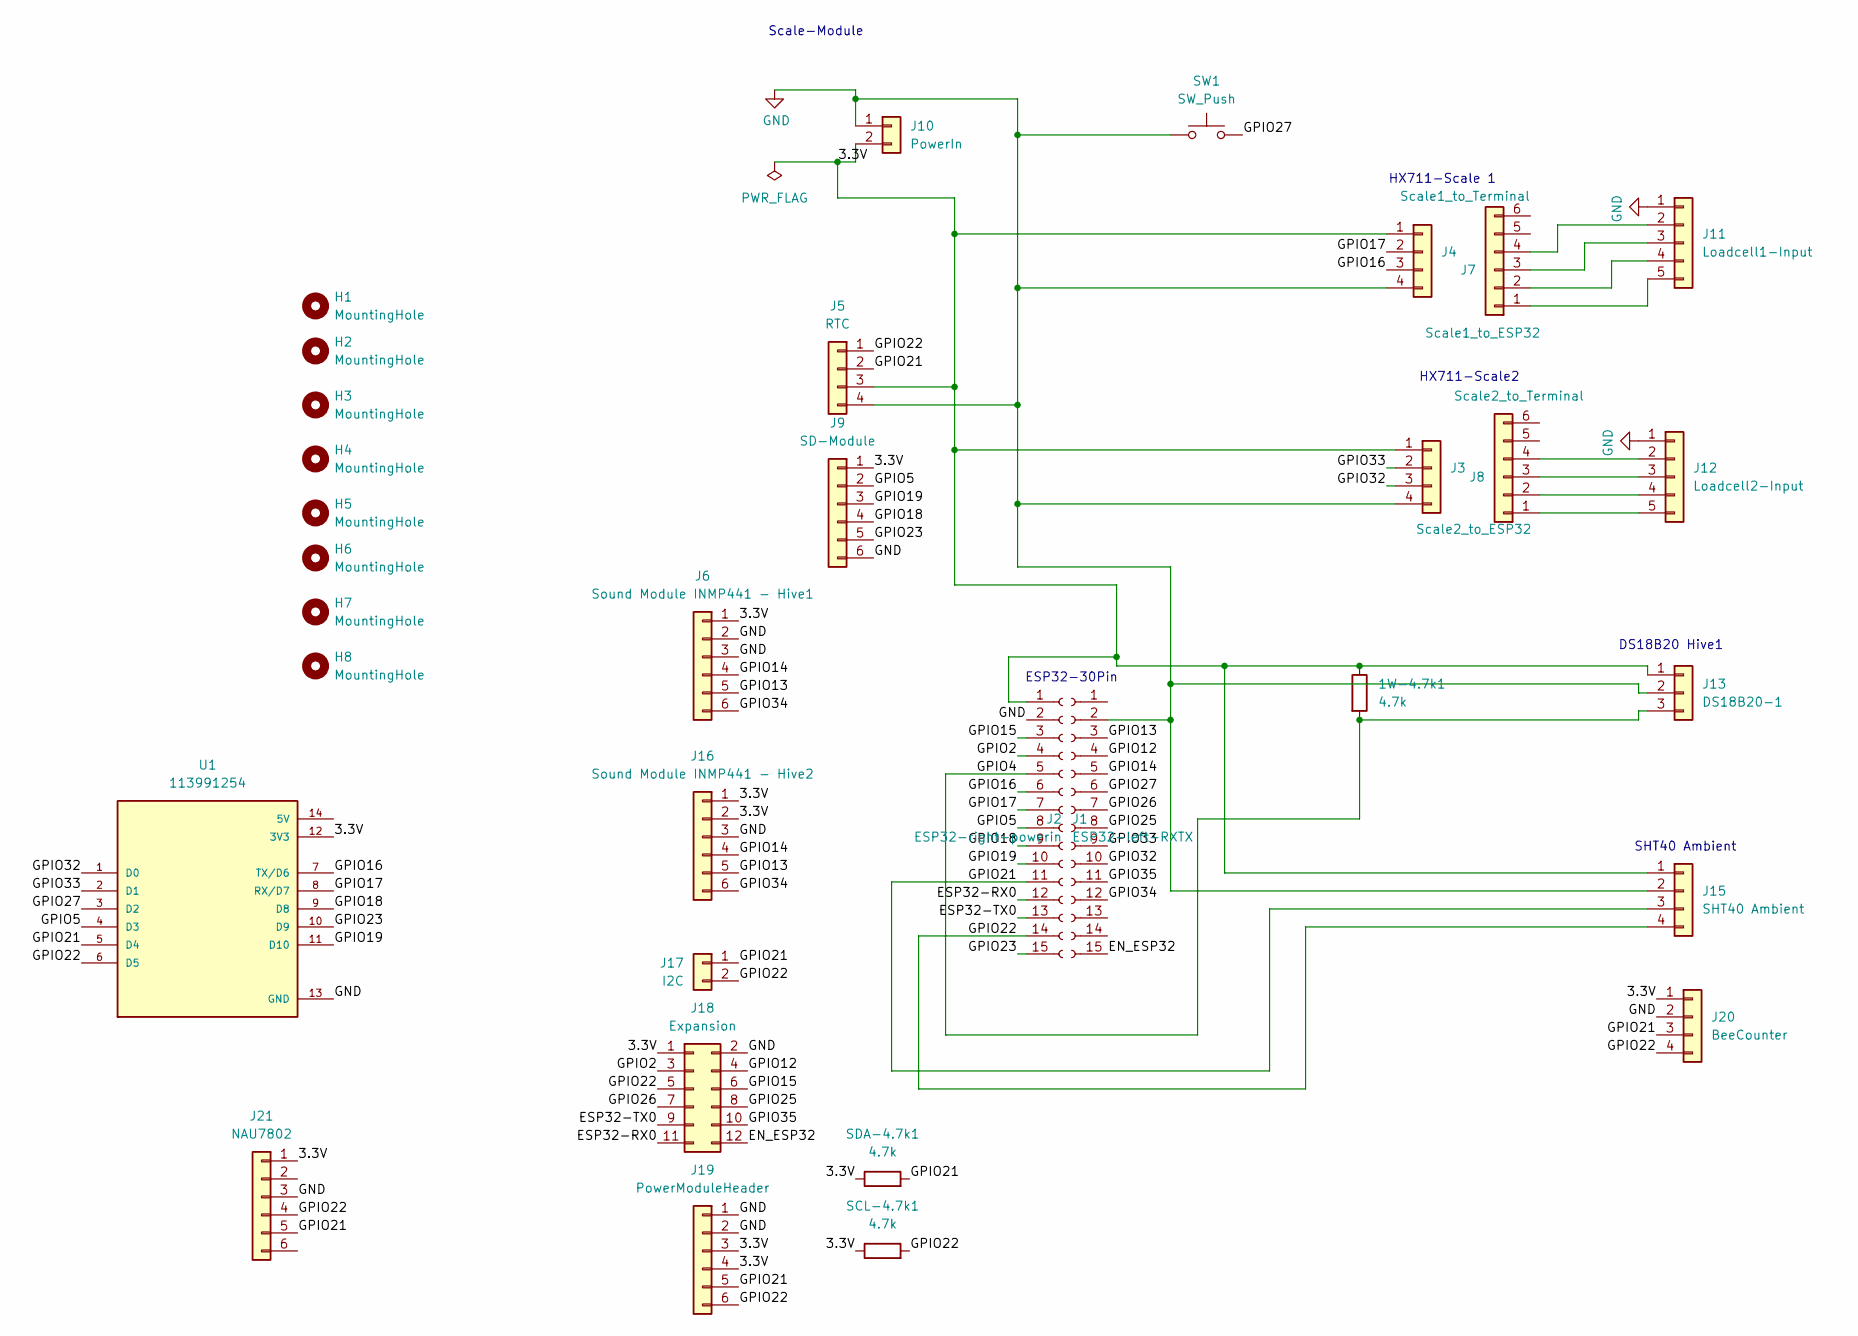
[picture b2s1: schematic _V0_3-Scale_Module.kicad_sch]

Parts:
1W-4.7k1: 4.7k; R_Axial_DIN0207_L6.3mm_D2.5mm_P7.62mm_Horizontal
H1, H2, H3, H4, H5, H6, H7, H8: MountingHole; MountingHole_3.2mm_M3
J1: ESP32-left-RXTX; PinSocket_1x15_P2.54mm_Vertical
J2: ESP32-right-powerin; PinHeader_1x15_P2.54mm_Vertical
J3: Scale2_to_ESP32; PinSocket_1x04_P2.54mm_Vertical
J4: Scale1_to_ESP32; PinSocket_1x04_P2.54mm_Vertical
J5: RTC; PinSocket_1x04_P2.54mm_Vertical
J6: Sound Module INMP441 - Hive1; JST_XH_B6B-XH-A_1x06_P2.50mm_Vertical
J7: Scale1_to_Terminal; PinSocket_1x06_P2.54mm_Vertical
J8: Scale2_to_Terminal; PinSocket_1x06_P2.54mm_Vertical
J9: SD-Module; PinSocket_1x06_P2.54mm_Vertical
J10: PowerIn; TerminalBlock_Xinya_XY308-2.54-2P_1x02_P2.54mm_Horizontal
J11: Loadcell1-Input; JST_XH_B5B-XH-A_1x05_P2.50mm_Vertical
J12: Loadcell2-Input; JST_XH_B5B-XH-A_1x05_P2.50mm_Vertical
J13: DS18B20-1; JST_XH_B3B-XH-A_1x03_P2.50mm_Vertical
J15: SHT40 Ambient; JST_XH_B4B-XH-A_1x04_P2.50mm_Vertical
J16: Sound Module INMP441 - Hive2; JST_XH_B6B-XH-A_1x06_P2.50mm_Vertical
J17: I2C; TerminalBlock_Xinya_XY308-2.54-2P_1x02_P2.54mm_Horizontal
J18: Expansion; PinHeader_2x06_P2.54mm_Vertical
J19: PowerModuleHeader; PinHeader_1x06_P2.54mm_Vertical
J20: BeeCounter; JST_XH_B4B-XH-A_1x04_P2.50mm_Vertical
J21: NAU7802; PinHeader_1x06_P2.54mm_Vertical
SCL-4.7k1: 4.7k; R_Axial_DIN0207_L6.3mm_D2.5mm_P7.62mm_Horizontal
SDA-4.7k1: 4.7k; R_Axial_DIN0207_L6.3mm_D2.5mm_P7.62mm_Horizontal
SW1: SW_Push; PinSocket_1x02_P2.54mm_Vertical
U1: 113991254; MODULE_113991254; PARTREV v1.0

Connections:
/3.3V: 1W-4.7k1.1, J1.1, J3.1, J4.1, J5.3, J6.1, J9.1, J10.2, J13.1, J15.1, J16.1, J16.2, J18.1, J19.3, J19.4, J20.1, J21.1, SCL-4.7k1.1, SDA-4.7k1.1, U1.12 (3V3)
/EN_ESP32: J2.15, J18.12
/ESP32-RX0: J1.12, J18.11
/ESP32-TX0: J1.13, J18.9
/GPIO2: J1.4, J18.3
/GPIO4: 1W-4.7k1.2, J1.5, J13.3
/GPIO5: J1.8, J9.2, U1.4 (D3)
/GPIO12: J2.4, J18.4
/GPIO13: J2.3, J6.5, J16.5
/GPIO14: J2.5, J6.4, J16.4
/GPIO15: J1.3, J18.6
/GPIO16: J1.6, J4.3, U1.7 (TX/D6)
/GPIO17: J1.7, J4.2, U1.8 (RX/D7)
/GPIO18: J1.9, J9.4, U1.9 (D8)
/GPIO19: J1.10, J9.3, U1.11 (D10)
/GPIO21: J1.11, J5.2, J15.3, J17.1, J19.5, J20.3, J21.5, SDA-4.7k1.2, U1.5 (D4)
/GPIO22: J1.14, J5.1, J15.4, J17.2, J18.5, J19.6, J20.4, J21.4, SCL-4.7k1.2, U1.6 (D5)
/GPIO23: J1.15, J9.5, U1.10 (D9)
/GPIO25: J2.8, J18.8
/GPIO26: J2.7, J18.7
/GPIO27: J2.6, SW1.2, U1.3 (D2)
/GPIO32: J2.10, J3.3, U1.1 (D0)
/GPIO33: J2.9, J3.2, U1.2 (D1)
/GPIO34: J2.12, J6.6, J16.6
/GPIO35: J2.11, J18.10
GND: J1.2, J2.2, J3.4, J4.4, J5.4, J6.2, J6.3, J9.6, J10.1, J11.1, J12.1, J13.2, J15.2, J16.3, J18.2, J19.1, J19.2, J20.2, J21.3, SW1.1, U1.13 (GND)
unnamed: J7.4, J11.2
unnamed: J7.3, J11.3
unnamed: J7.2, J11.4
unnamed: J7.1, J11.5
unnamed: J8.4, J12.2
unnamed: J8.3, J12.3
unnamed: J8.2, J12.4
unnamed: J8.1, J12.5

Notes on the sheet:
Scale-Module
HX711-Scale2
DS18B20 Hive1
SHT40 Ambient
ESP32-30Pin
HX711-Scale 1

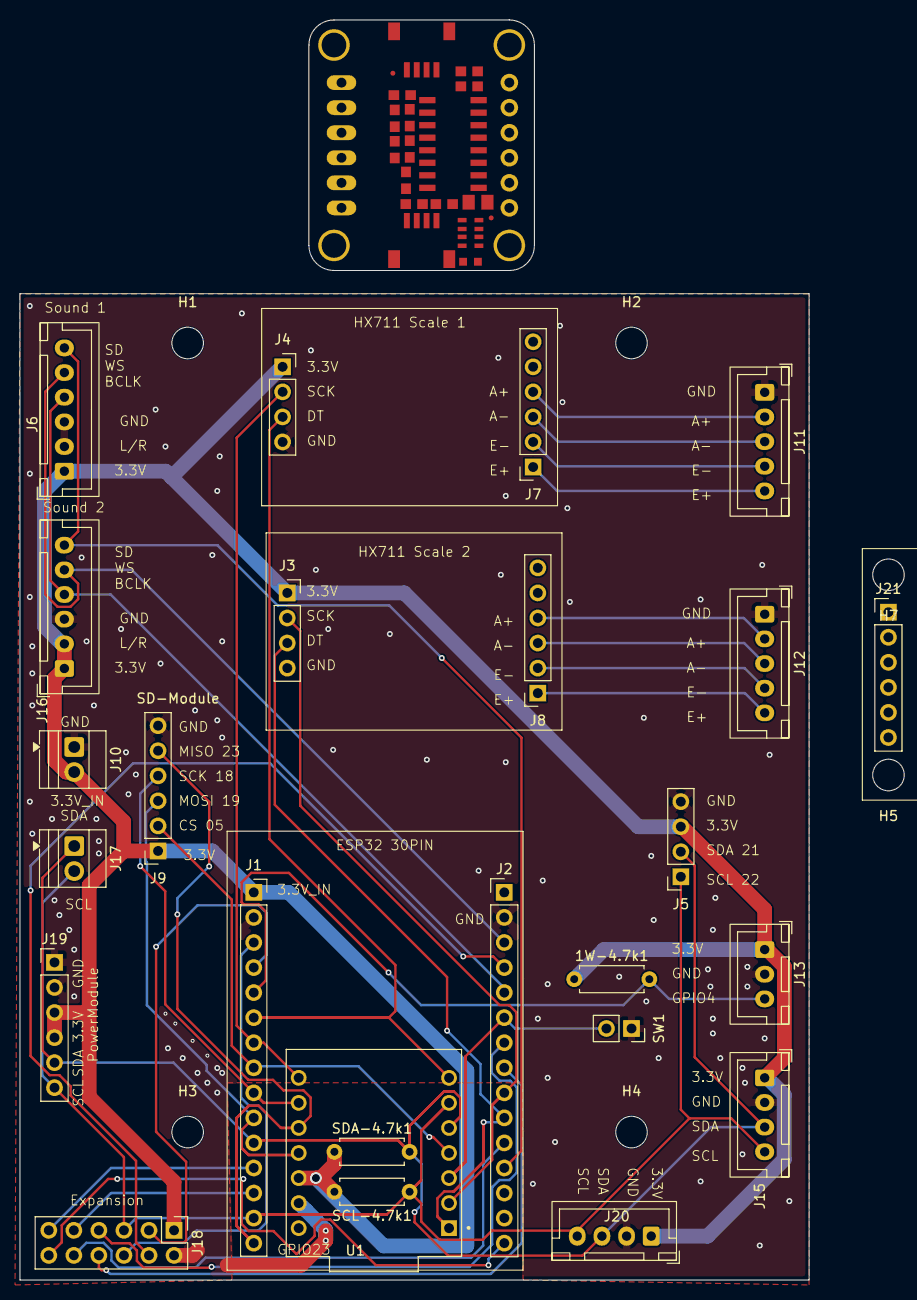
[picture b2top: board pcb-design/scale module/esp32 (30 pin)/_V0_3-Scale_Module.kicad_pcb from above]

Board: 2 copper layers, 80.0 x 127.7 mm, 33 parts (0 on the bottom side), 34 nets.

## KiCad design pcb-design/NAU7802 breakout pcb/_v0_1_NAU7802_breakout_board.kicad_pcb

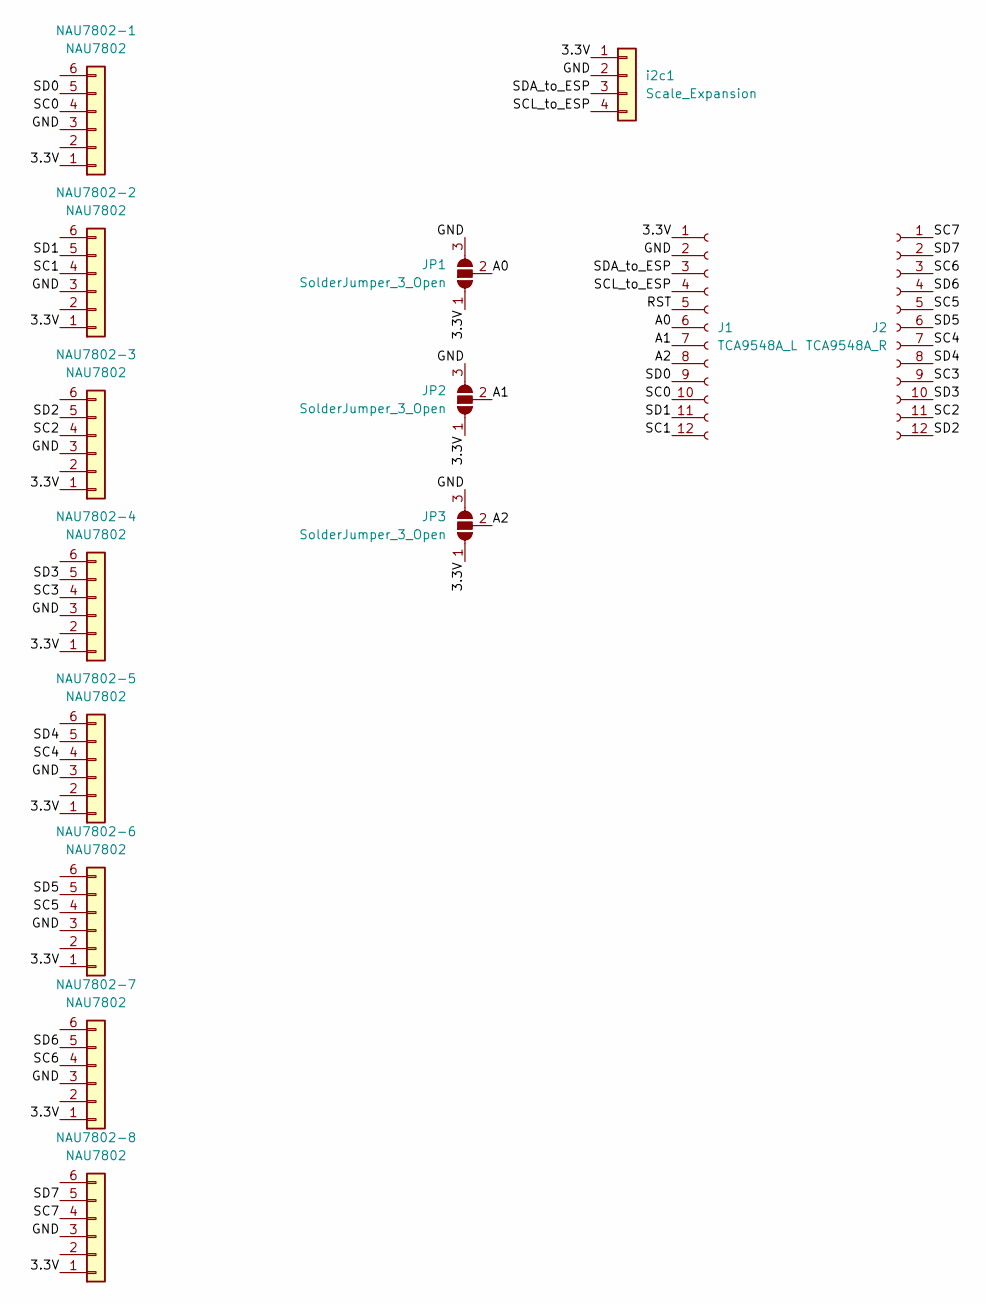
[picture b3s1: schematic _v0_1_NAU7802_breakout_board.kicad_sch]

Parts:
J1: TCA9548A_L; PinSocket_1x12_P2.54mm_Vertical
J2: TCA9548A_R; PinSocket_1x12_P2.54mm_Vertical
JP1, JP2, JP3: SolderJumper_3_Open; SolderJumper-3_P1.3mm_Open_Pad1.0x1.5mm_NumberLabels
NAU7802-1, NAU7802-2, NAU7802-3, NAU7802-4, NAU7802-5, NAU7802-6, NAU7802-7, NAU7802-8: NAU7802
i2c1: Scale_Expansion; TerminalBlock_Xinya_XY308-2.54-4P_1x04_P2.54mm_Horizontal

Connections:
/3.3V: J1.1, JP1.1 (A), JP2.1 (A), JP3.1 (A), NAU7802-1.1, NAU7802-2.1, NAU7802-3.1, NAU7802-4.1, NAU7802-5.1, NAU7802-6.1, NAU7802-7.1, NAU7802-8.1, i2c1.1
/A0: J1.6, JP1.2 (C)
/A1: J1.7, JP2.2 (C)
/A2: J1.8, JP3.2 (C)
/GND: J1.2, JP1.3 (B), JP2.3 (B), JP3.3 (B), NAU7802-1.3, NAU7802-2.3, NAU7802-3.3, NAU7802-4.3, NAU7802-5.3, NAU7802-6.3, NAU7802-7.3, NAU7802-8.3, i2c1.2
/RST: J1.5
/SC0: J1.10, NAU7802-1.4
/SC1: J1.12, NAU7802-2.4
/SC2: J2.11, NAU7802-3.4
/SC3: J2.9, NAU7802-4.4
/SC4: J2.7, NAU7802-5.4
/SC5: J2.5, NAU7802-6.4
/SC6: J2.3, NAU7802-7.4
/SC7: J2.1, NAU7802-8.4
/SCL_to_ESP: J1.4, i2c1.4
/SD0: J1.9, NAU7802-1.5
/SD1: J1.11, NAU7802-2.5
/SD2: J2.12, NAU7802-3.5
/SD3: J2.10, NAU7802-4.5
/SD4: J2.8, NAU7802-5.5
/SD5: J2.6, NAU7802-6.5
/SD6: J2.4, NAU7802-7.5
/SD7: J2.2, NAU7802-8.5
/SDA_to_ESP: J1.3, i2c1.3

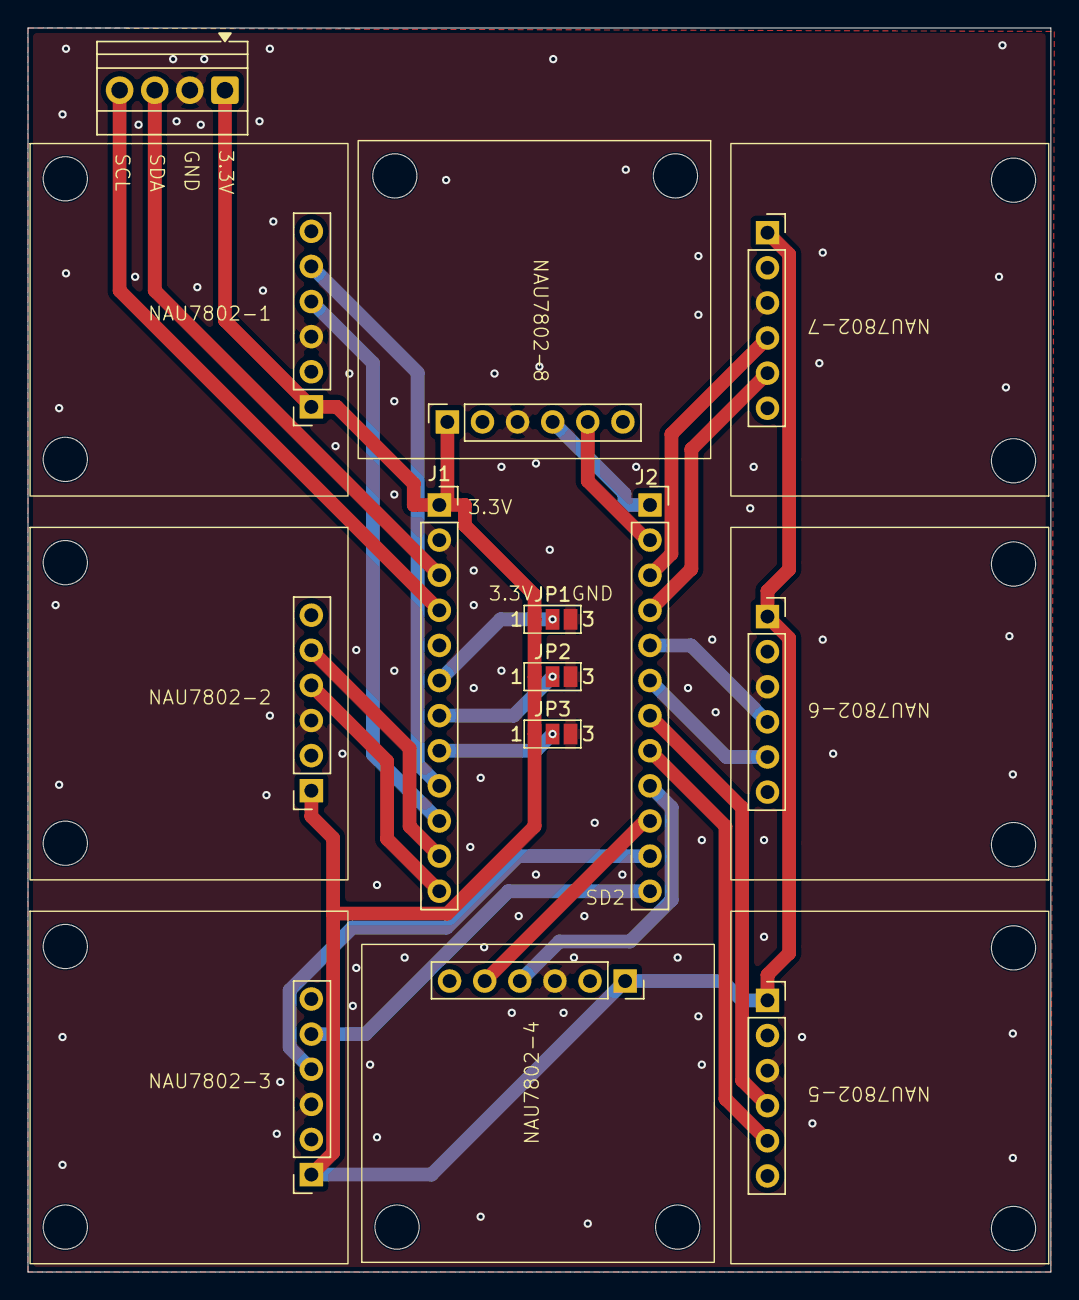
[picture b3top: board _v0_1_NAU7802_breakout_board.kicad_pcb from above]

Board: 2 copper layers, 74.0 x 90.0 mm, 14 parts (0 on the bottom side), 23 nets.

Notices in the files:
README.md:
License:
MIT © 2026 Maximilian Nitschke
